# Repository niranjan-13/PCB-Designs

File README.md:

# PCB-Designs
Included PCB Designs in EAGLE software.

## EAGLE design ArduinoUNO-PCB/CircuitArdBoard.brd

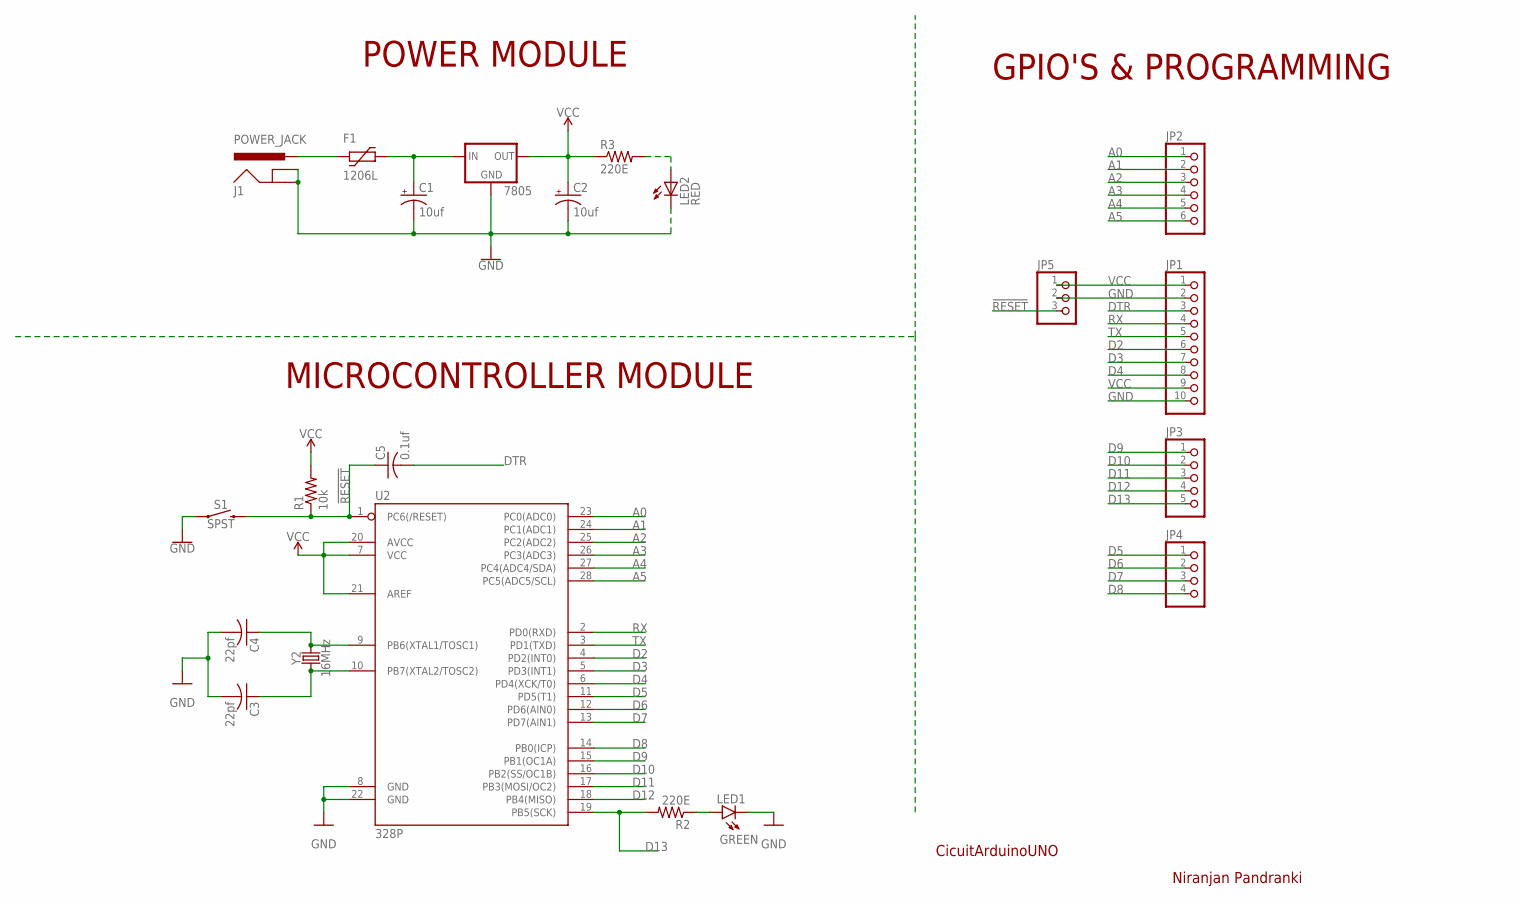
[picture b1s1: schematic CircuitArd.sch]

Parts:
C1, C2: 10uf; E2,5-6E
C3, C4: 22pf; C025-024X044
C5: 0.1uf; C025-024X044
F1: 1206L
IC1: 7805; 78XXS
J1: POWER_JACK; POWER_JACK_PTH
JP1: PINHD-1X10; 1X10
JP2: PINHD-1X6; 1X06
JP3: PINHD-1X5; 1X05
JP4: PINHD-1X4; 1X04
JP5: PINHD-1X3; 1X03
LED1: GREEN; LED3MM
LED2: RED; LED3MM
R1: 10k; 0204/7
R2, R3: 220E; 0204/7
S1: SPST; TACTILE_SWITCH_PTH_6.0MM
U2: 328P; DIP28
Y2: 16MHz; HC49US

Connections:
!RESET: C5.1, JP5.3, R1.1, S1.3 (2), U2.1 (PC6(/RESET))
A0: JP2.1, U2.23 (PC0(ADC0))
A1: JP2.2, U2.24 (PC1(ADC1))
A2: JP2.3, U2.25 (PC2(ADC2))
A3: JP2.4, U2.26 (PC3(ADC3))
A4: JP2.5, U2.27 (PC4(ADC4/SDA))
A5: JP2.6, U2.28 (PC5(ADC5/SCL))
D2: JP1.6, U2.4 (PD2(INT0))
D3: JP1.7, U2.5 (PD3(INT1))
D4: JP1.8, U2.6 (PD4(XCK/T0))
D5: JP4.1, U2.11 (PD5(T1))
D6: JP4.2, U2.12 (PD6(AIN0))
D7: JP4.3, U2.13 (PD7(AIN1))
D8: JP4.4, U2.14 (PB0(ICP))
D9: JP3.1, U2.15 (PB1(OC1A))
D10: JP3.2, U2.16 (PB2(SS/OC1B))
D11: JP3.3, U2.17 (PB3(MOSI/OC2))
D12: JP3.4, U2.18 (PB4(MISO))
D13: JP3.5, R2.2, U2.19 (PB5(SCK))
DTR: C5.2, JP1.3
GND: C1.-, C2.-, C3.2, C4.2, IC1.GND, J1.GND, J1.GNDBREAK, JP1.2, JP1.10, JP5.2, LED1.K (C), LED2.K (C), S1.1, U2.8 (GND), U2.22 (GND)
unnamed: C1.+, F1.P$2 (2), IC1.IN
unnamed: C3.1, U2.10 (PB7(XTAL2/TOSC2)), Y2.1
unnamed: C4.1, U2.9 (PB6(XTAL1/TOSC1)), Y2.2
unnamed: LED1.A, R2.1
unnamed: LED2.A, R3.2
unnamed: F1.P$1 (1), J1.PWR
RX: JP1.4, U2.2 (PD0(RXD))
TX: JP1.5, U2.3 (PD1(TXD))
VCC: C2.+, IC1.OUT, JP1.1, JP1.9, JP5.1, R1.2, R3.1, U2.7 (VCC), U2.20 (AVCC), U2.21 (AREF)

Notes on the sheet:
POWER MODULE
GPIO'S & PROGRAMMING
MICROCONTROLLER MODULE
CicuitArduinoUNO
Niranjan Pandranki

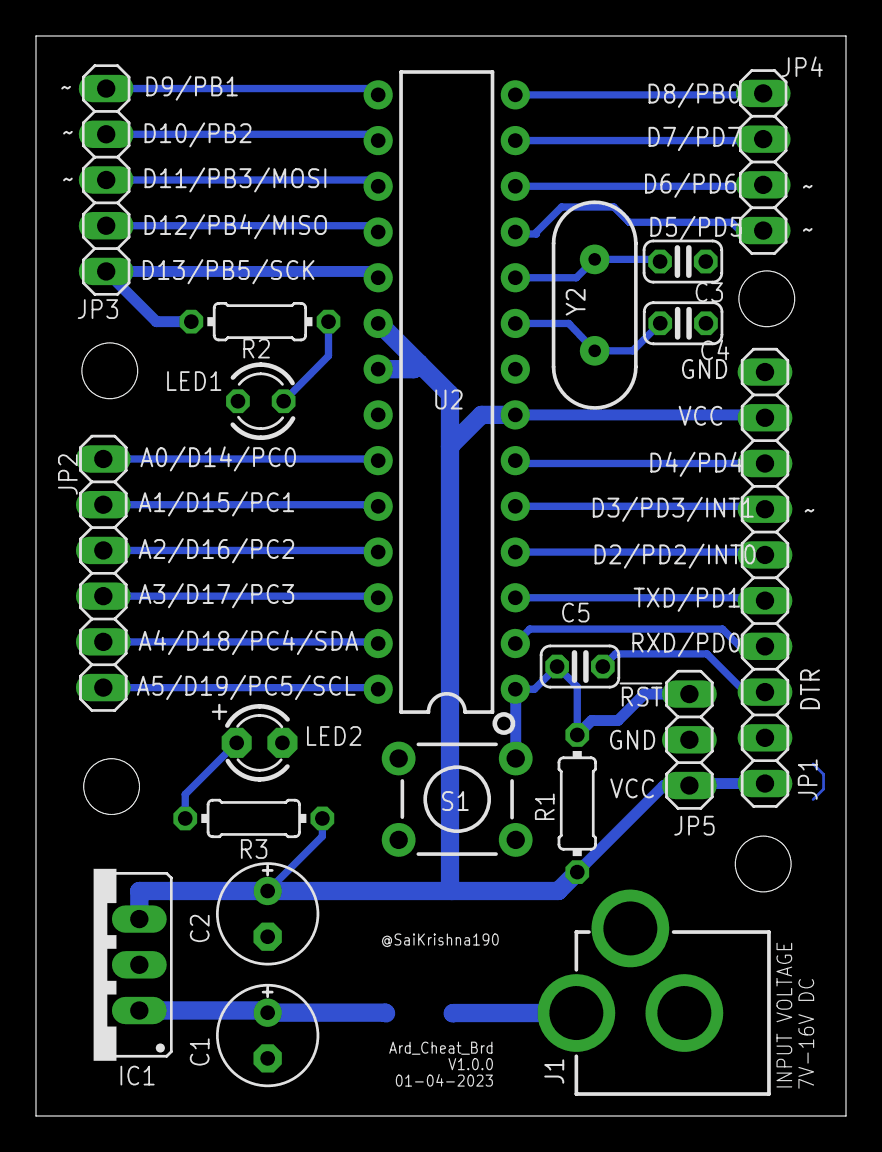
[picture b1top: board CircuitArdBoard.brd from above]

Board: 2 copper layers, 45.0 x 60.0 mm, 21 parts (1 on the bottom side), 30 nets.

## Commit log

2023-07-20 Added New PCB design

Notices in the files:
parts and their libraries:
SparkFun-Connectors: Licensing: Creative Commons ShareAlike 4.0 International - https://creativecommons.org/licenses/by-sa/4.0
